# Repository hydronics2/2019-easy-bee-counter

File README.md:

# 2019 Easy Bee Counter V.1

This version of the bee counter is easy to solder and assemble (all through-hole).  It's been tested and works* with sample code provided.

The current tested design is easy to program and approachable to beginner programmers.  The printed circuit board accepts multiple Arduino platforms made by Adafruit including their line of [Adafruit Feather](https://www.adafruit.com/category/777) type micro-controllers and [Adafruit ItsyBitsy](https://www.adafruit.com/category/1008) micro-controllers.   The Adafruit feathers include wifi and long range radio features (*~~esp8266~~, esp32, and **LoRA). All the ItsyBitsy 3V models (M0, M4, and 32u4) should work fine.

*the esp8266 is missing A5 so you have to jumper to another pin
**see below issue with SPI

### [Data Analysis - *why count bees?](https://github.com/hydronics2/2019-easy-bee-counter/blob/master/Data/README.md)
### [Instructions](https://github.com/hydronics2/2019-easy-bee-counter/blob/master/instructions/README.md)
### [Arduino Code](https://github.com/hydronics2/2019-easy-bee-counter/blob/master/arduino/README.md)
### Major Differences/Improvements
- All through-hole components for easy soldering
- Dual footprint, socketed, off-the-shelf micro-controllers => Feather and ItsyBitsy
- Program in Arduino, Lua, and microPython
- A total of 24 gates, 48 sensors, 6 shift registers
- ~14.75" long stretching the entire opening of a langstroth hive for easy placement
- using 2 PCBs to create a sandwich is an inexpensive quick solution. The PCBs must be ordered [black](https://github.com/hydronics2/2019-easy-bee-counter/tree/master/instructions/ordering_instructions) so the IR LED emitter is absorbed into the material.
- using 6 pin headers to create the turn-styles or gates
- N-Ch mosfet controlled IR LEDs such that LEDs can be controlled ON for short periods during while sensing (~75us). Allows for reduced power to less than 1ma (plus micro-controller).

### General Operation
Honeybees are forced through 24 gates where optical sensors (48 sensors) determine whether the bee is present and determine the direction of the bee movement. Each optical sensors has an IR LED and an IR sensor. If no bee is present the IR light is absorbed into the black surface. If a bee is present the IR light reflects off the bee and triggers the sensor. 

### Micro-Controller Pinout
#### Feather ESP32 Pinout

#### ItsyBitsy Pinout

### Shift-in registers
There are 6 shift-in registers. Here's a great description for how to connect and program [shift registers](http://www.gammon.com.au/forum/?id=11979).  The micro-controller's SPI pins read the shift registers. All six shift registers are read at the same time. The sensors are normally pulled low and show 3.3V or HIGH when a transistor is triggered and a bee is present.

Unfortunately the shift registers we're using (the most popular shift register chip!) are not [full SPI devices](https://electronics.stackexchange.com/questions/121249/how-to-put-a-74hc165-on-an-spi-bus) and wont share the SPI with other devices.. They're like the worst SPI devices!... therefore some boards like the Adalogger or LoRa just wont work out of the box. You can still do it by cutting some traces and patching the SPI lines to free pins and bitbanging the SPI to the shift registers.. buy yeah not optimum. You can get a true-spi shift register but the pinout will be different than the 74hc165 used here.

### IR LEDs
The 48 LEDs are divided into two sets of 24 with each set controlled by an N-ch mosfet. The normal forward voltage of each IR LED is 1.2V and about 20ma as shown on the [data sheet](https://www.sparkfun.com/datasheets/Robotics/QR_QRE1113.GR.pdf). Two LEDs are connected in series with a 22ohm resistor. There are jumpers on the board that allow the LEDs to bypass the current limiting resistors. Do not solder the jumper until fully tested! Refer to [these instructions](https://github.com/hydronics2/2019-easy-bee-counter/tree/master/instructions)

### Power
The PCB design connects the USB power pin from the uController to the 3.3V regulator so that a usb cable connected to the micro-controller can power the entire project.

### Bill of Materials
#### uController
The code was tested with the feather esp32 Huzzah and itsyBitsy M0 but will work with all these boards.
- feather Huzzah from [mouser](https://www.mouser.com/ProductDetail/485-3591)
- feather esp8266 from [mouser](https://www.mouser.com/ProductDetail/485-2821)
  - the esp8266 is missing A5, so if this micro is used you have to jumper to another pin
- feather LoRa 900mhz from [mouser](https://www.mouser.com/ProductDetail/485-3178)
- ItsyBitsy M0 from [mouser](https://www.mouser.com/ProductDetail/485-3727)
- ItsyBitsy M4 from [mouser](https://www.mouser.com/ProductDetail/485-3800)
#### PCB
[JLCPCB](https://jlcpcb.com/quote#/) ~$16-25 with shipping. Order the PCBs Black. See [these instructions](https://github.com/hydronics2/2019-easy-bee-counter/tree/master/instructions/ordering_instructions) for ordering.
#### Parts and Pieces from [mouser](https://www.mouser.com/ProjectManager/ProjectDetail.aspx?AccessID=054286973a)
See alternative pricing below for cheaper options specifically for the reflectance sensors.
- [qre1113 Reflective Sensors](https://www.mouser.com/ProductDetail/512-QRE1113f) qty(48)
- [6 pin female headers](https://www.mouser.com/ProductDetail/437-8018700610001101) 7mm high, 0.1" spacing, qty(~36)
- [22ohm resistors](https://www.mouser.com/ProductDetail/Xicon/266-22-RC?qs=sGAEpiMZZMvrmc6UYKmaNXFefT4dxyTCwtpTxTI0yoo%3D), bussed, qty(4)
SIP Packaged, bussed
- [100k ohm resistors](https://www.mouser.com/ProductDetail/IRC-TT-Electronics/L091S104LF?qs=sGAEpiMZZMvrmc6UYKmaNdnTrsZX%2FuSiyGduauH5Qpc%3D) bussed, qty(6)
SIP-9, 8 resistors, 9 pins
- Shift registers, qty(6)
[74HC165](https://www.mouser.com/ProductDetail/595-SN74HC165N)
- [3.3V Regulator](https://www.mouser.com/ProductDetail/Microchip-Technology/MCP1826S-3302E-AB?qs=sGAEpiMZZMsGz1a6aV8DcJ7KfjtCj7Xd5CqQpyOghgk%3D), (input, ground, output - IGO, pinout), qty(1)
- [screw terminals](https://www.mouser.com/ProductDetail/490-TB006-508-02BE) Two pin, 0.1", qty(3)
- [0.1 uF Ceramic Capacitor](https://www.mouser.com/ProductDetail/594-K104K15X7RF53H5), through hole, qty(6)
- [1 uF Ceramic Capacitor](https://www.mouser.com/ProductDetail/594-K105Z20Y5VF5TL2), through hole, qty(1)
- [560uF, 6.3V Capacitor](https://www.mouser.com/ProductDetail/661-APSC6R3L561MH08S)
low esr, 3.5mm lead spacing, 8mm diameter
- N-Channel Mosfet [FQP30N06](https://www.mouser.com/ProductDetail/512-FQP30N06L), qty(2)
  - [chinswain](https://github.com/hydronics2/2019-easy-bee-counter/issues/20#issuecomment-2094117078) suggested using this IRLB8721PbF N-Channel mosfet. He suggested the signal threshold of 3.3V was not sufficient to meet the gate threshold for the FQP30N06L... and it could be the ebay versions of the FQP30N06L floating around are not to spec.

#### Alternative pricing from Chinese distributor LCSC
Someone pointed out some alternative pricing that can really bring the cost down.
- [ITR8307 Reflectance Sensors](https://lcsc.com/product-detail/Photo-Interrupter_Everlight-Elec-ITR8307_C63451.html) ~$0.13/each @ qty(48) (same as QRE1113)
- [6 pin female headers](https://lcsc.com/product-detail/Pin-Header-Female-Header_BOOMELE-Boom-Precision-Elec-C40877_C40877.html) 8.5mm high. ~$0.05/each @ qty(36+)
- [22 ohm SIP](https://lcsc.com/product-detail/Resistor-Networks-Arrays_FH-Guangdong-Fenghua-Advanced-Tech-A09-220JP_C9105.html) 8 resistor, 9 pin, it will fit. $0.44 for qty(4)
- [100k SIP Resistors](https://lcsc.com/product-detail/Resistor-Networks-Arrays_FH-Guangdong-Fenghua-Advanced-Tech-A09-104JP_C9108.html) 8 resistor, 9pin, it will fit. $0.44 for qty(6)

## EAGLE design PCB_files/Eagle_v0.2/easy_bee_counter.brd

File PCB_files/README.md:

## Printed Circuit Board (PCB)

This PCB version has two footprints that accept the wider (0.8") Adafruit Feather micro-controllers such as the [esp32](https://www.adafruit.com/product/3405) and the narrower (0.6")[Adafruit ItsyBitsy](https://www.adafruit.com/category/1008) micro-controllers.

**UPDATE** The GERBER files were developed from the kicad board files so had to remove the gerber files. You now have to use the Eagle board files or generate gerber files from the eagle board files.... or a lot of PCB manufacturers will take eagle PCB files and you don't have to generate your own gerber files. You can still use the kicad files but you have to route a small trace for the SCK pin. See this bug report: https://github.com/hydronics2/2019-easy-bee-counter/issues/25 

These files were created in Autocad EAGLE PCB software. The zipped files are the gerber files needed by the PCB manufacturer.

Right click and 'save link as' to download the files and then upload them to the PCB manufacturer. See the [ordering instructions here](https://github.com/hydronics2/2019-easy-bee-counter/tree/master/instructions/ordering_instructions). Most board shops require a minimum order of 3-5 boards and you'll need 2 boards to sandwich together to complete one bee counter.

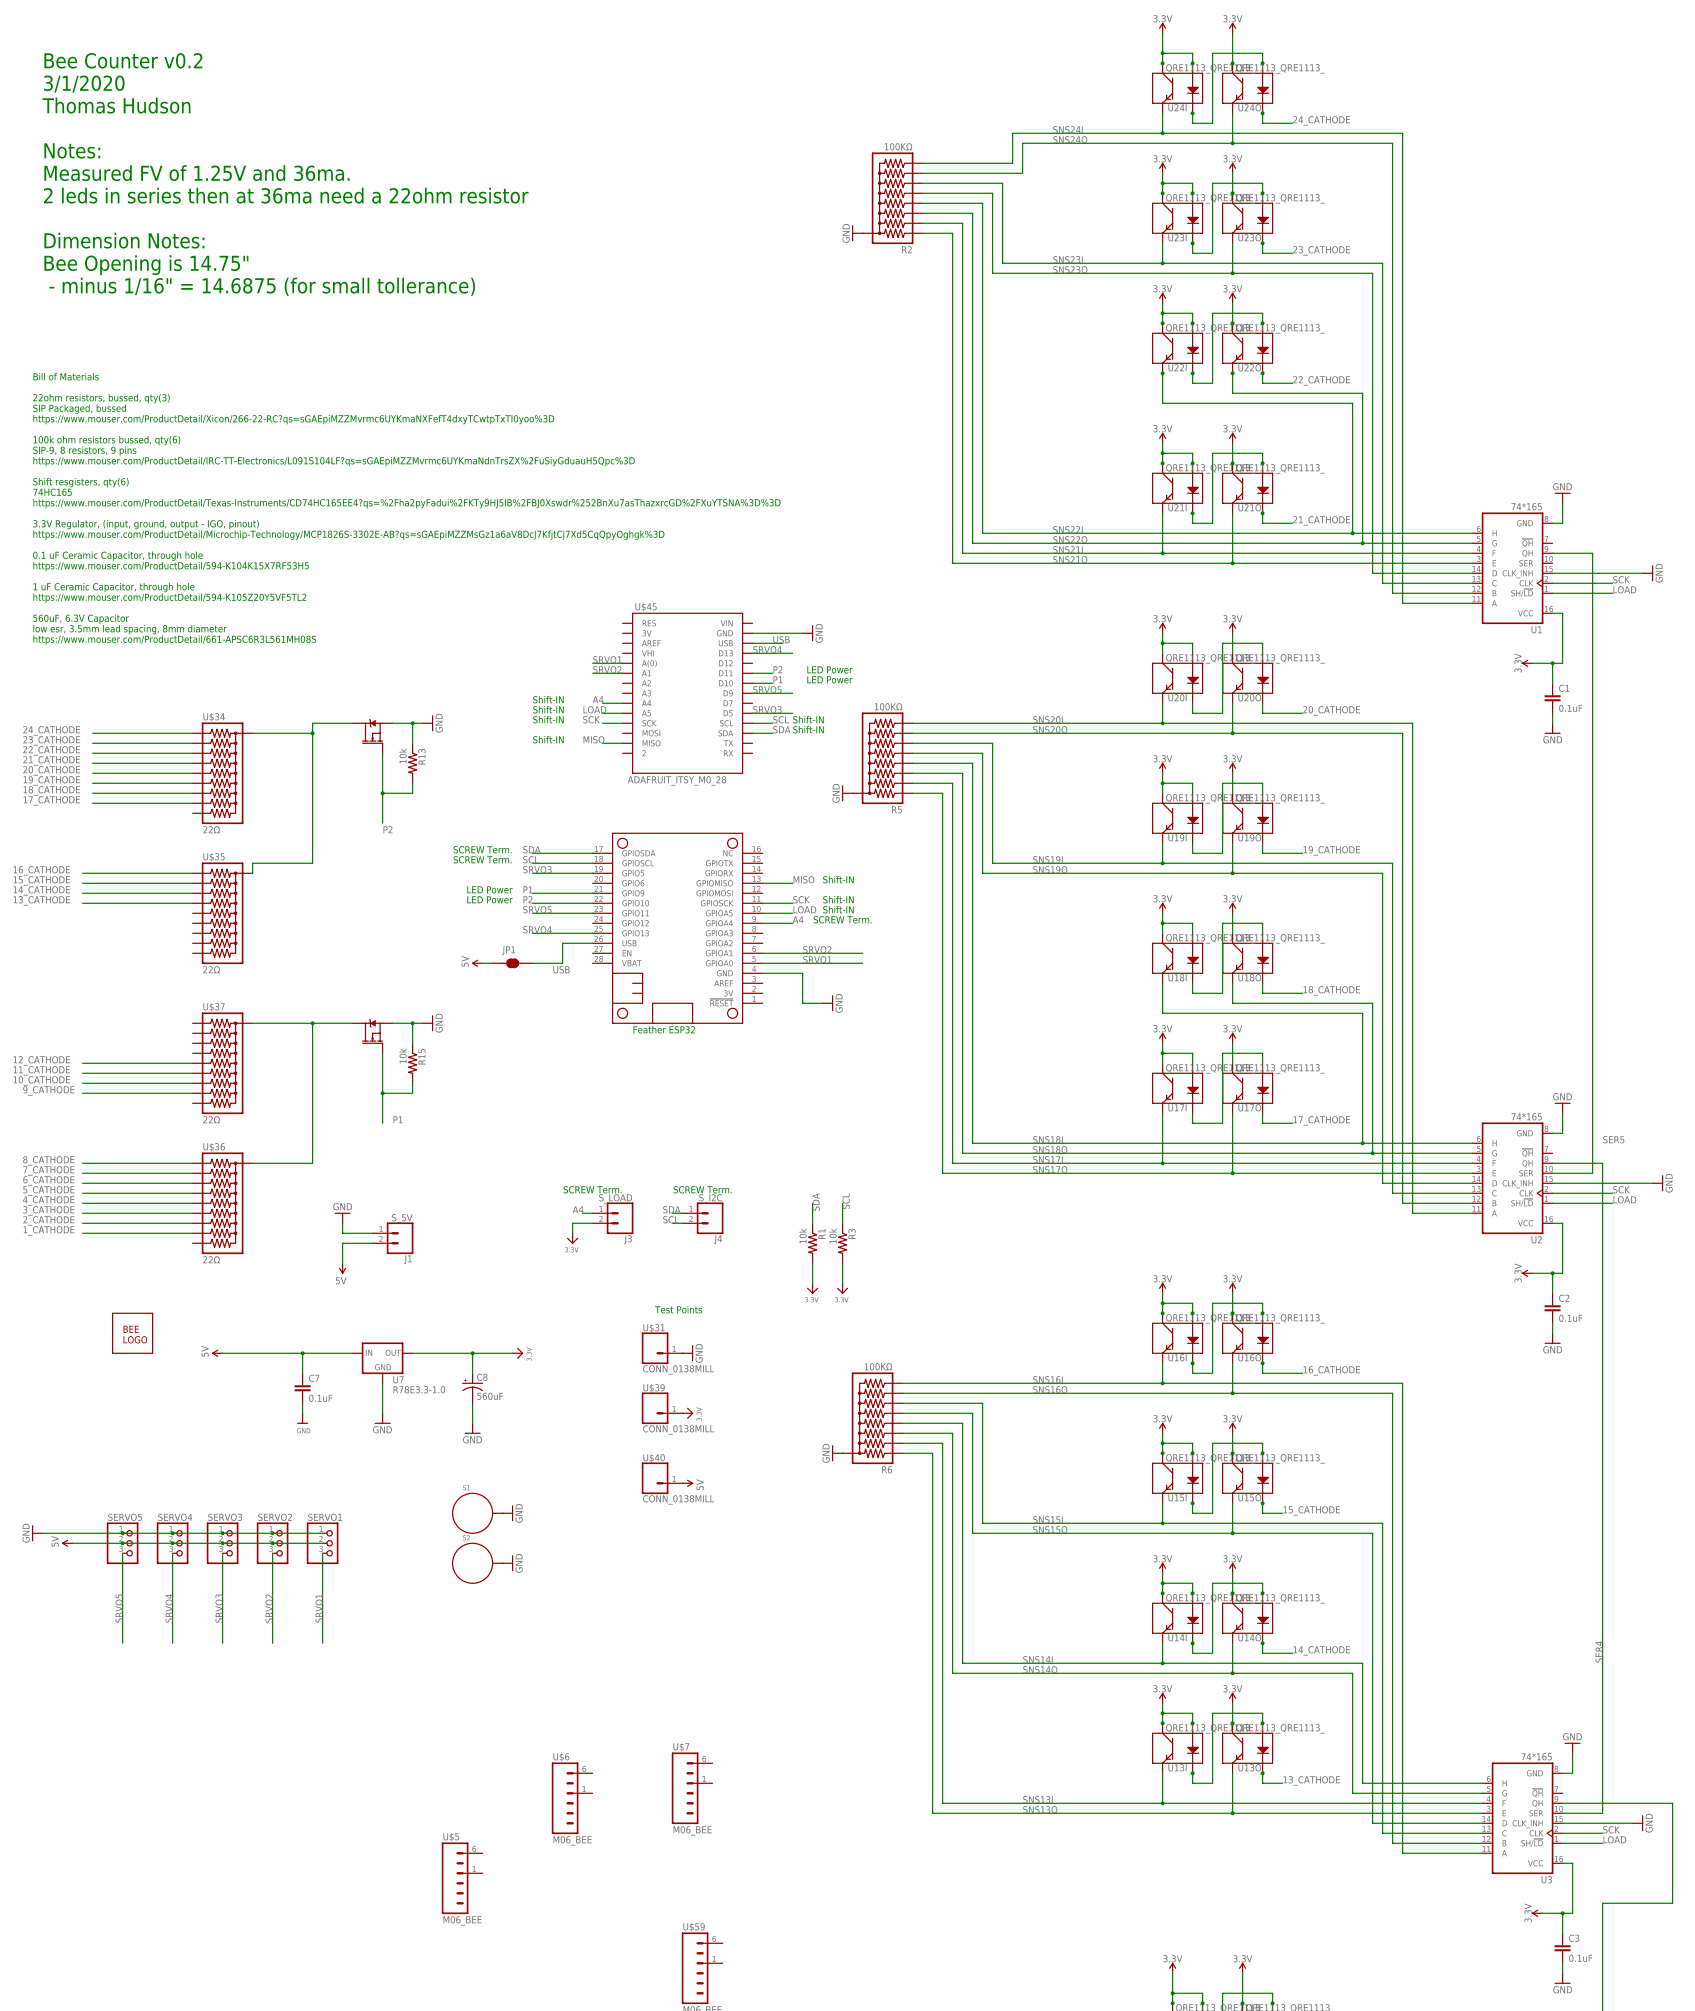
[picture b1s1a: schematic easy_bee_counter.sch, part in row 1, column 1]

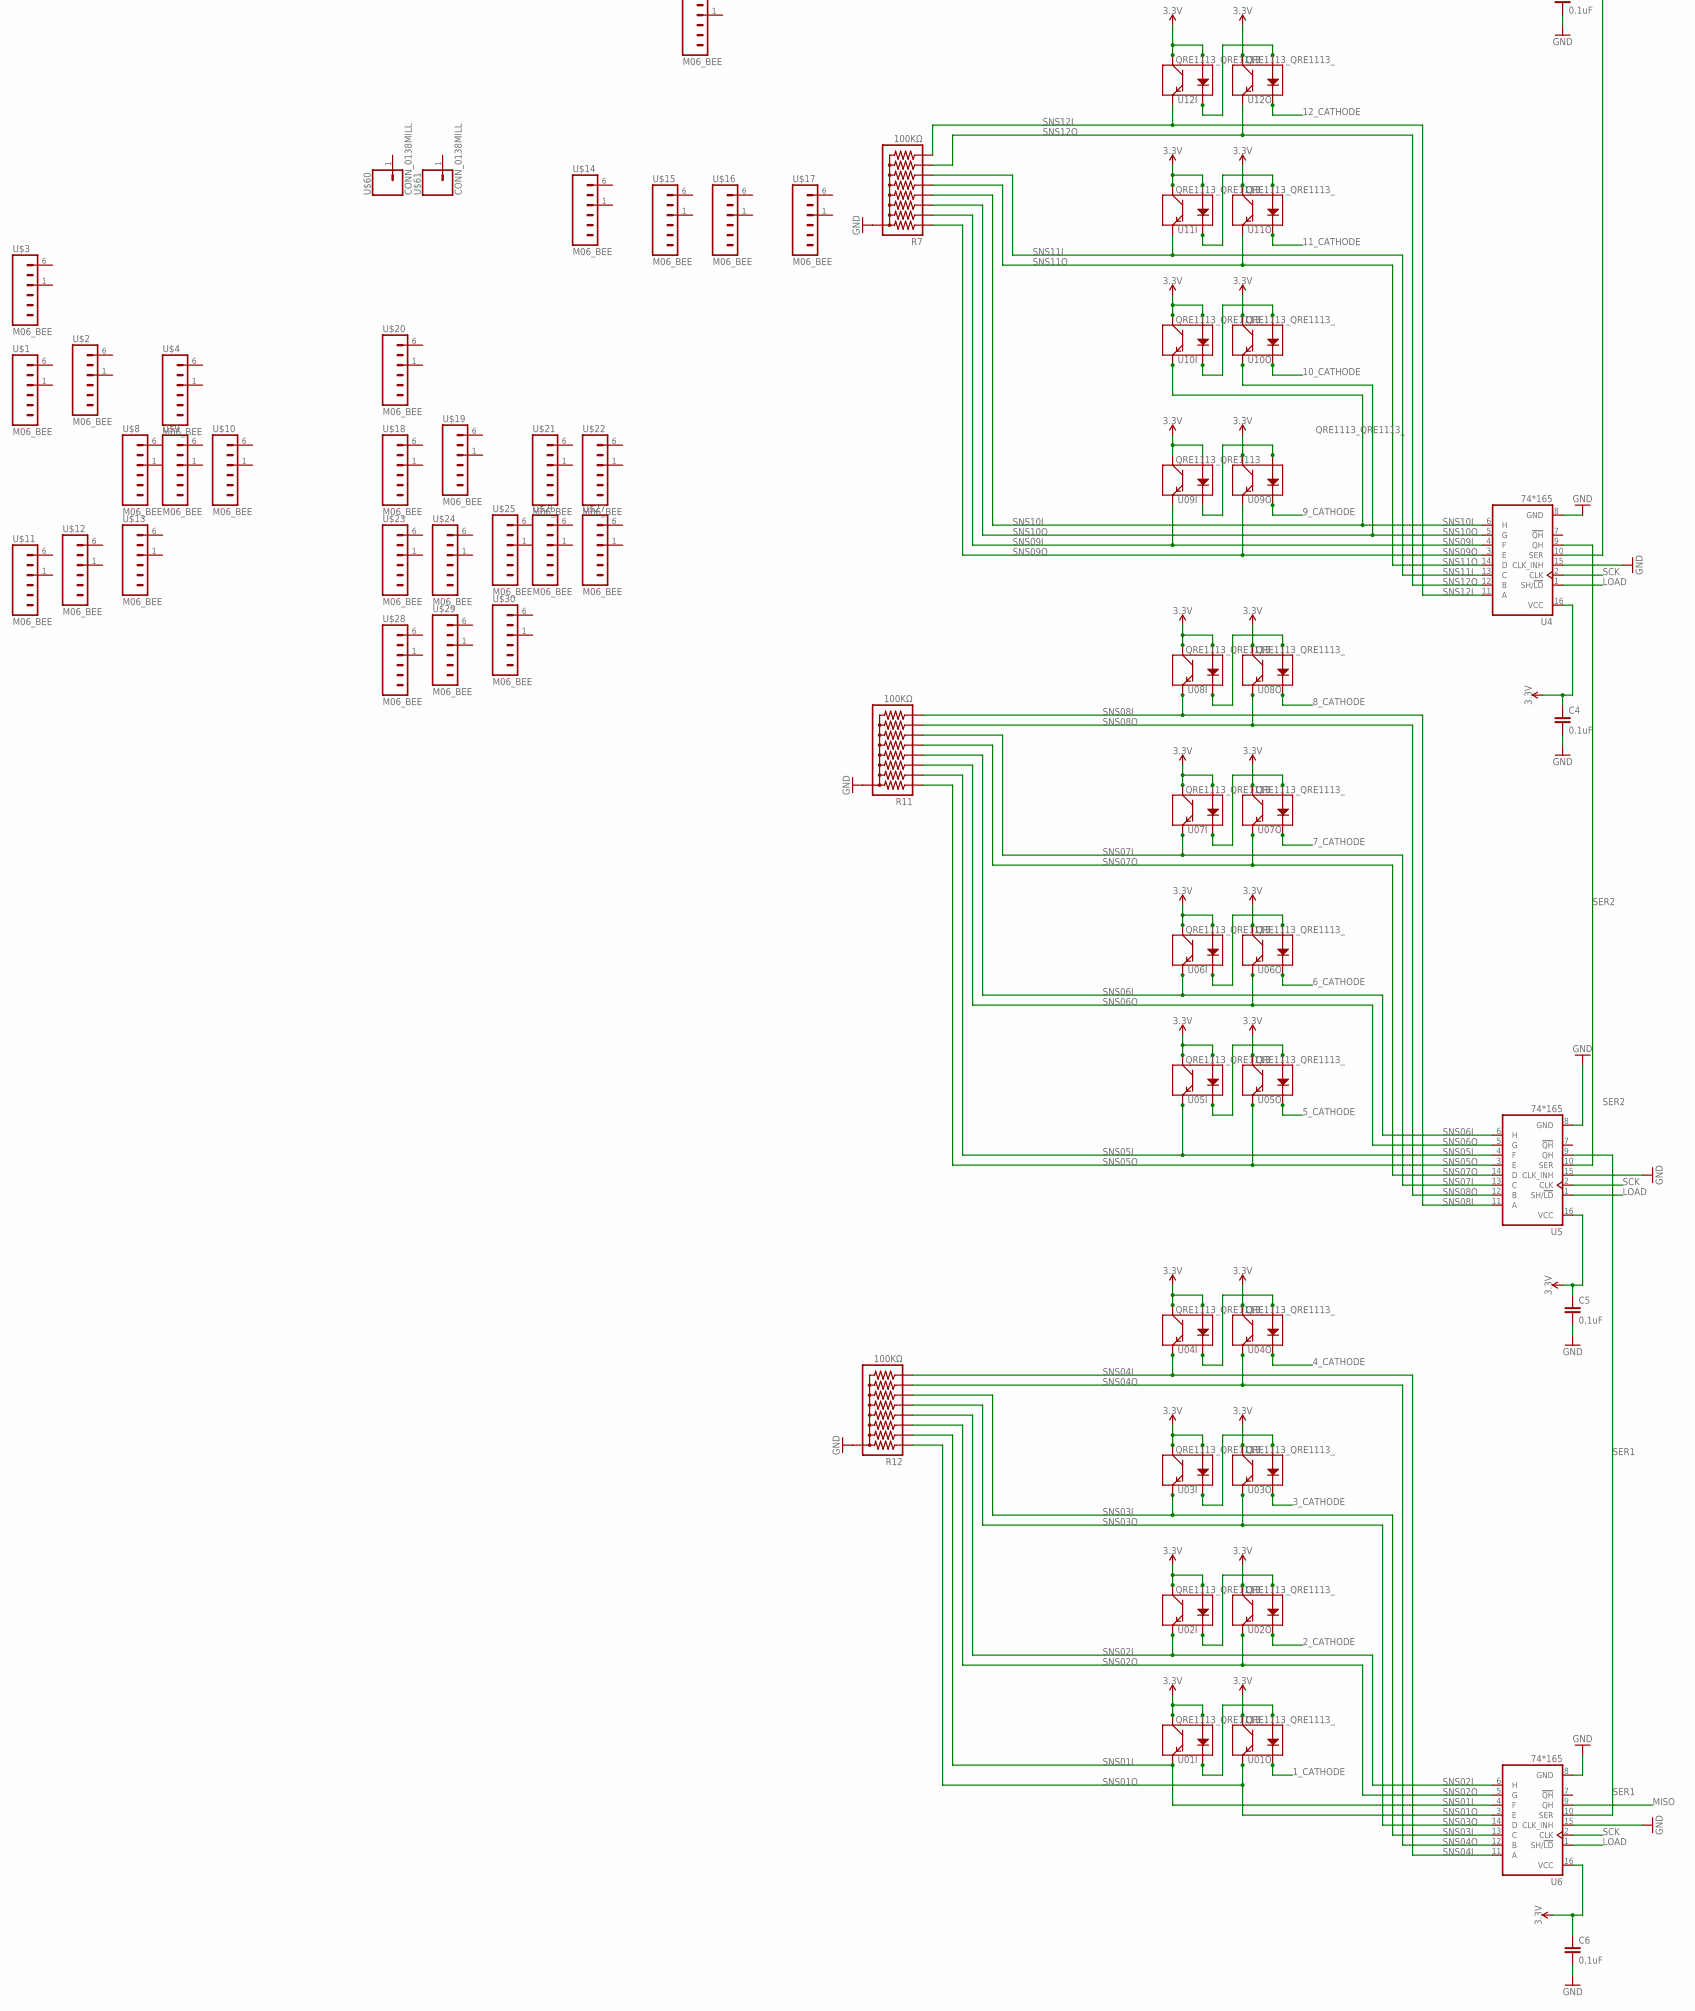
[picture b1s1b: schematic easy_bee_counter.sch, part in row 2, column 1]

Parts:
C1, C2, C3, C4, C5, C6, C7: 0.1uF; CAP-PTH-SMALL-KIT
C8: 560uF; E3,5-8
J1: S_5V; SCREWTERMINAL-5MM-2
J3: S_LOAD; SCREWTERMINAL-5MM-2
J4: S_I2C; SCREWTERMINAL-5MM-2
JP1: JUMPER-SMT_2_NC_TRACE_SILK; SMT-JUMPER_2_NC_TRACE_SILK
MS2: FEATHERWING_NODIM; FEATHERWING_DIM
Q6, Q7: 60V/32A/35mΩ; TO220V
R1, R3, R13, R15: 10k; AXIAL-0.3
R2, R5, R6, R7, R11, R12: 100KΩ; RPACK-SIP-PTH-8
S1, S2: STANDOFF_ELECTRICAL5-32; STANDOFF_ELECTRICAL_5_32
SERVO1, SERVO2, SERVO3, SERVO4, SERVO5: PINHD-1X3; 1X03
U1, U2, U3, U4, U5, U6: 74*165; DIP16
U01I, U01O, U02I, U02O, U03I, U03O, U04I, U04O, U05I, U05O, U06I, U06O, U07I, U07O, U08I, U08O, U09I, U09O, U10I, U10O, U11I, U11O, U12I, U12O, U13I, U13O, U14I, U14O, U15I, U15O, U16I, U16O, U17I, U17O, U18I, U18O, U19I, U19O, U20I, U20O, U21I, U21O, U22I, U22O, U23I, U23O, U24I, U24O: QRE1113_QRE1113_; QRE1113_DIP400W50P180L360H200Q4
U7: R78E3.3-1.0; DC-DC_CONVERTER_78XX
U$1, U$2, U$3, U$4, U$5, U$6, U$7, U$8, U$9, U$10, U$11, U$12, U$13, U$14, U$15, U$16, U$17, U$18, U$19, U$20, U$21, U$22, U$23, U$24, U$25, U$26, U$27, U$28, U$29, U$30, U$59: M06_BEE; 1X06_BEE
U$31, U$39, U$40, U$60, U$61: CONN_0138MILL; 1X01-40MILL
U$34, U$35, U$36, U$37: 22Ω; RPACK-SIP-PTH-9
U$44: BEE_LOGO
U$45: ADAFRUIT_ITSY_M0_28; ADAFRUIT_ITS_MO_28

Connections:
1_CATHODE: U01O.2 (K), U$36.P$9 (9)
2_CATHODE: U02O.2 (K), U$36.P$8 (8)
3.3V: C1.1, C2.1, C3.1, C4.1, C5.1, C6.1, C8.+, J3.2, R1.P$2 (2), R3.P$2 (2), U1.16 (VCC), U01I.1 (A), U01I.3 (C), U01O.3 (C), U2.16 (VCC), U02I.1 (A), U02I.3 (C), U02O.3 (C), U3.16 (VCC), U03I.1 (A), U03I.3 (C), U03O.3 (C), U4.16 (VCC), U04I.1 (A), U04I.3 (C), U04O.3 (C), U5.16 (VCC), U05I.1 (A), U05I.3 (C), U05O.3 (C), U6.16 (VCC), U06I.1 (A), U06I.3 (C), U06O.3 (C), U7.VOUT (OUT), U07I.1 (A), U07I.3 (C), U07O.3 (C), U08I.1 (A), U08I.3 (C), U08O.3 (C), U09I.1 (A), U09I.3 (C), U09O.3 (C), U10I.1 (A), U10I.3 (C), U10O.3 (C), U11I.1 (A), U11I.3 (C), U11O.3 (C), U12I.1 (A), U12I.3 (C), U12O.3 (C), U13I.1 (A), U13I.3 (C), U13O.3 (C), U14I.1 (A), U14I.3 (C), U14O.3 (C), U15I.1 (A), U15I.3 (C), U15O.3 (C), U16I.1 (A), U16I.3 (C), U16O.3 (C), U17I.1 (A), U17I.3 (C), U17O.3 (C), U18I.1 (A), U18I.3 (C), U18O.3 (C), U19I.1 (A), U19I.3 (C), U19O.3 (C), U20I.1 (A), U20I.3 (C), U20O.3 (C), U21I.1 (A), U21I.3 (C), U21O.3 (C), U22I.1 (A), U22I.3 (C), U22O.3 (C), U23I.1 (A), U23I.3 (C), U23O.3 (C), U24I.1 (A), U24I.3 (C), U24O.3 (C), U$39.1
3_CATHODE: U03O.2 (K), U$36.P$7 (7)
4_CATHODE: U04O.2 (K), U$36.P$6 (6)
5V: C7.1, J1.2, JP1.1, SERVO1.2, SERVO2.2, SERVO3.2, SERVO4.2, SERVO5.2, U7.VIN (IN), U$40.1
5_CATHODE: U05O.2 (K), U$36.P$5 (5)
6_CATHODE: U06O.2 (K), U$36.P$4 (4)
7_CATHODE: U07O.2 (K), U$36.P$3 (3)
8_CATHODE: U08O.2 (K), U$36.P$2 (2)
9_CATHODE: U09O.2 (K), U$37.P$9 (9)
10_CATHODE: U10O.2 (K), U$37.P$8 (8)
11_CATHODE: U11O.2 (K), U$37.P$7 (7)
12_CATHODE: U12O.2 (K), U$37.P$6 (6)
13_CATHODE: U13O.2 (K), U$35.P$5 (5)
14_CATHODE: U14O.2 (K), U$35.P$4 (4)
15_CATHODE: U15O.2 (K), U$35.P$3 (3)
16_CATHODE: U16O.2 (K), U$35.P$2 (2)
17_CATHODE: U17O.2 (K), U$34.P$9 (9)
18_CATHODE: U18O.2 (K), U$34.P$8 (8)
19_CATHODE: U19O.2 (K), U$34.P$7 (7)
20_CATHODE: U20O.2 (K), U$34.P$6 (6)
21_CATHODE: U21O.2 (K), U$34.P$5 (5)
22_CATHODE: U22O.2 (K), U$34.P$4 (4)
23_CATHODE: U23O.2 (K), U$34.P$3 (3)
24_CATHODE: U24O.2 (K), U$34.P$2 (2)
A4: J3.1, MS2.9 (GPIOA4), U$45.A4
GND: C1.2, C2.2, C3.2, C4.2, C5.2, C6.2, C7.2, C8.-, J1.1, MS2.4 (GND), Q6.3 (S), Q7.3 (S), R2.P$1 (1), R5.P$1 (1), R6.P$1 (1), R7.P$1 (1), R11.P$1 (1), R12.P$1 (1), R13.P$1 (1), R15.P$1 (1), S1.P1, S2.P1, SERVO1.1, SERVO2.1, SERVO3.1, SERVO4.1, SERVO5.1, U1.8 (GND), U1.15 (CLK_INH), U2.8 (GND), U2.15 (CLK_INH), U3.8 (GND), U3.15 (CLK_INH), U4.8 (GND), U4.15 (CLK_INH), U5.8 (GND), U5.15 (CLK_INH), U6.8 (GND), U6.15 (CLK_INH), U7.GND, U$31.1, U$45.GND
LOAD: MS2.10 (GPIOA5), U1.1 (SH/!LD), U2.1 (SH/!LD), U3.1 (SH/!LD), U4.1 (SH/!LD), U5.1 (SH/!LD), U6.1 (SH/!LD), U$45.A5
MISO: MS2.13 (GPIOMISO), U6.9 (QH), U$45.MISO
unnamed: U11I.2 (K), U11O.1 (A)
unnamed: U12I.2 (K), U12O.1 (A)
unnamed: U10I.2 (K), U10O.1 (A)
unnamed: U09I.2 (K), U09O.1 (A)
unnamed: U05I.2 (K), U05O.1 (A)
unnamed: U06I.2 (K), U06O.1 (A)
unnamed: U08I.2 (K), U08O.1 (A)
unnamed: U04I.2 (K), U04O.1 (A)
unnamed: U07I.2 (K), U07O.1 (A)
unnamed: U03I.2 (K), U03O.1 (A)
unnamed: U02I.2 (K), U02O.1 (A)
unnamed: U01I.2 (K), U01O.1 (A)
unnamed: U24I.2 (K), U24O.1 (A)
unnamed: U23I.2 (K), U23O.1 (A)
unnamed: U22I.2 (K), U22O.1 (A)
unnamed: U21I.2 (K), U21O.1 (A)
unnamed: U17I.2 (K), U17O.1 (A)
unnamed: U18I.2 (K), U18O.1 (A)
unnamed: U20I.2 (K), U20O.1 (A)
unnamed: U19I.2 (K), U19O.1 (A)
unnamed: U16I.2 (K), U16O.1 (A)
unnamed: U15I.2 (K), U15O.1 (A)
unnamed: U14I.2 (K), U14O.1 (A)
unnamed: U13I.2 (K), U13O.1 (A)
P1: MS2.21 (GPIO9), Q7.1 (G), R15.P$2 (2), U$45.D10
P2: MS2.22 (GPIO10), Q6.1 (G), R13.P$2 (2), U$45.D11
PWR_1-12: Q7.2 (D), U$36.P$1 (1), U$37.P$1 (1)
PWR_13-24: Q6.2 (D), U$34.P$1 (1), U$35.P$1 (1)
SCK: MS2.11 (GPIOSCK), U1.2 (CLK), U2.2 (CLK), U3.2 (CLK), U4.2 (CLK), U5.2 (CLK), U6.2 (CLK), U$45.SCK
SCL: J4.2, MS2.18 (GPIOSCL), R3.P$1 (1), U$45.SCL
SDA: J4.1, MS2.17 (GPIOSDA), R1.P$1 (1), U$45.SDA
SER1: U5.9 (QH), U6.10 (SER)
SER2: U4.9 (QH), U5.10 (SER)
SER3: U3.9 (QH), U4.10 (SER)
SER4: U2.9 (QH), U3.10 (SER)
SER5: U1.9 (QH), U2.10 (SER)
SNS01I: R12.P$3 (3), U01I.4 (E), U6.4 (F)
SNS01O: R12.P$2 (2), U01O.4 (E), U6.3 (E)
SNS02I: R12.P$5 (5), U02I.4 (E), U6.6 (H)
SNS02O: R12.P$4 (4), U02O.4 (E), U6.5 (G)
SNS03I: R12.P$7 (7), U03I.4 (E), U6.13 (C)
SNS03O: R12.P$6 (6), U03O.4 (E), U6.14 (D)
SNS04I: R12.P$9 (9), U04I.4 (E), U6.11 (A)
SNS04O: R12.P$8 (8), U04O.4 (E), U6.12 (B)
SNS05I: R11.P$3 (3), U5.4 (F), U05I.4 (E)
SNS05O: R11.P$2 (2), U5.3 (E), U05O.4 (E)
SNS06I: R11.P$5 (5), U5.6 (H), U06I.4 (E)
SNS06O: R11.P$4 (4), U5.5 (G), U06O.4 (E)
SNS07I: R11.P$7 (7), U5.13 (C), U07I.4 (E)
SNS07O: R11.P$6 (6), U5.14 (D), U07O.4 (E)
SNS08I: R11.P$9 (9), U5.11 (A), U08I.4 (E)
SNS08O: R11.P$8 (8), U5.12 (B), U08O.4 (E)
SNS09I: R7.P$3 (3), U4.4 (F), U09I.4 (E)
SNS09O: R7.P$2 (2), U4.3 (E), U09O.4 (E)
SNS10I: R7.P$5 (5), U4.6 (H), U10I.4 (E)
SNS10O: R7.P$4 (4), U4.5 (G), U10O.4 (E)
SNS11I: R7.P$7 (7), U4.13 (C), U11I.4 (E)
SNS11O: R7.P$6 (6), U4.14 (D), U11O.4 (E)
SNS12I: R7.P$9 (9), U4.11 (A), U12I.4 (E)
SNS12O: R7.P$8 (8), U4.12 (B), U12O.4 (E)
SNS13I: R6.P$3 (3), U3.4 (F), U13I.4 (E)
SNS13O: R6.P$2 (2), U3.3 (E), U13O.4 (E)
SNS14I: R6.P$5 (5), U3.6 (H), U14I.4 (E)
SNS14O: R6.P$4 (4), U3.5 (G), U14O.4 (E)
SNS15I: R6.P$7 (7), U3.13 (C), U15I.4 (E)
SNS15O: R6.P$6 (6), U3.14 (D), U15O.4 (E)
SNS16I: R6.P$9 (9), U3.11 (A), U16I.4 (E)
SNS16O: R6.P$8 (8), U3.12 (B), U16O.4 (E)
SNS17I: R5.P$3 (3), U2.4 (F), U17I.4 (E)
SNS17O: R5.P$2 (2), U2.3 (E), U17O.4 (E)
SNS18I: R5.P$5 (5), U2.6 (H), U18I.4 (E)
SNS18O: R5.P$4 (4), U2.5 (G), U18O.4 (E)
SNS19I: R5.P$7 (7), U2.13 (C), U19I.4 (E)
SNS19O: R5.P$6 (6), U2.14 (D), U19O.4 (E)
SNS20I: R5.P$9 (9), U2.11 (A), U20I.4 (E)
SNS20O: R5.P$8 (8), U2.12 (B), U20O.4 (E)
SNS21I: R2.P$3 (3), U1.4 (F), U21I.4 (E)
SNS21O: R2.P$2 (2), U1.3 (E), U21O.4 (E)
SNS22I: R2.P$5 (5), U1.6 (H), U22I.4 (E)
SNS22O: R2.P$4 (4), U1.5 (G), U22O.4 (E)
SNS23I: R2.P$7 (7), U1.13 (C), U23I.4 (E)
SNS23O: R2.P$6 (6), U1.14 (D), U23O.4 (E)
SNS24I: R2.P$9 (9), U1.11 (A), U24I.4 (E)
SNS24O: R2.P$8 (8), U1.12 (B), U24O.4 (E)
SRVO1: MS2.5 (GPIOA0), SERVO1.3, U$45.A0 (A(0))
SRVO2: MS2.6 (GPIOA1), SERVO2.3, U$45.A1
SRVO3: MS2.19 (GPIO5), SERVO3.3, U$45.D5
SRVO4: MS2.25 (GPIO13), SERVO4.3, U$45.D13
SRVO5: MS2.23 (GPIO11), SERVO5.3, U$45.D9
USB: JP1.2, MS2.26 (USB), U$45.USB

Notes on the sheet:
Notes: Measured FV of 1.25V and 36ma. 2 leds in series then at 36ma need a 22ohm resistor Dimension Notes: Bee Opening is 14.75" - minus 1/16" = 14.6875 (for small tollerance)
Bill of Materials 22ohm resistors, bussed, qty(3) SIP Packaged, bussed https://www.mouser.com/ProductDetail/Xicon/266-22-RC?qs=sGAEpiMZZMvrmc6UYKmaNXFefT4dxyTCwtpTxTI0yoo%3D 100k ohm resistors bussed, qty(6) SIP-9, 8 resistors, 9 pins https://www.mouser.com/ProductDetail/IRC-TT-Electronics/L091S104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
Shift-IN
LED Power
SCREW Term.
Test Points
Feather ESP32
Bee Counter v0.2 3/1/2020 Thomas Hudson

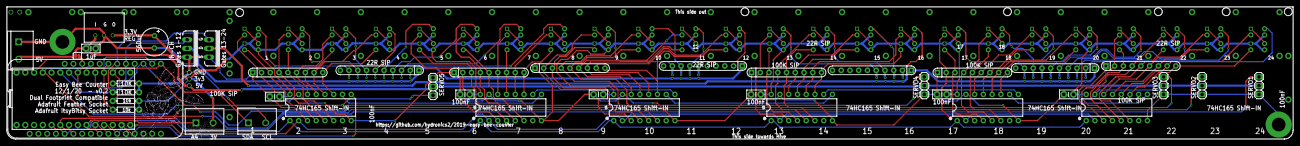
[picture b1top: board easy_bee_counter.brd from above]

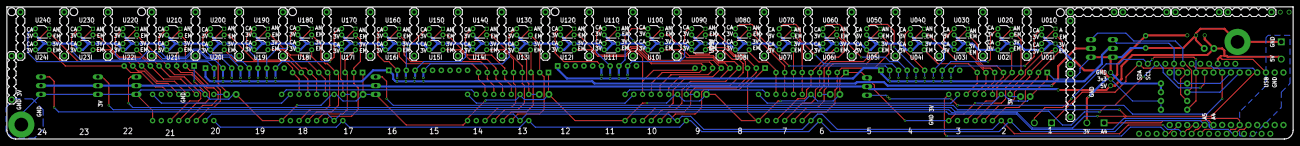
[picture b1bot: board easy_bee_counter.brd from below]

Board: 2 copper layers, 373.4 x 38.4 mm, 129 parts (79 on the bottom side), 120 nets.

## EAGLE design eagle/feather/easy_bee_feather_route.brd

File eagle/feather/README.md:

## FEATEHER Footrprint

This PCB version has a footprint for an Adafruit Feather such as the [esp32](https://www.adafruit.com/product/3405).

These files were created in Autocad EAGLE PCB software. The zipped files are the gerber files needed by the PCB manufacturer.

Right click and 'save link as' to download the files and then upload them to the PCB manufacturer. See the [ordering instructions here](https://github.com/hydronics2/2019-easy-bee-counter/tree/master/instructions/ordering_instructions)

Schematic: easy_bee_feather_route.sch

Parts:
C1, C2, C3, C4, C5, C6: 0.1uF; CAP-PTH-SMALL-KIT
C7: 1uF; CAP-PTH-SMALL-KIT
C8: 560uF; E3,5-8
J1, J3, J4: CONN_025MM; SCREWTERMINAL-5MM-2
JP1: JUMPER-SMT_2_NC_TRACE_SILK; SMT-JUMPER_2_NC_TRACE_SILK
MS2: FEATHERWING_NODIM; FEATHERWING_DIM
Q6, Q7: 60V/32A/35mΩ; TO220V
R2, R5, R6, R7, R11, R12: RPACK-BUSSED-8-SIP-PTH-8; RPACK-SIP-PTH-8
R13, R15: 10k; AXIAL-0.3
S1, S2: STANDOFF_ELECTRICAL5-32; STANDOFF_ELECTRICAL_5_32
U1, U2, U3, U4, U5, U6: 74165; DIP16
U7: V_REG_78XXSINK; TO220-IGO
U$1, U$2, U$3, U$4, U$5, U$6, U$7, U$8, U$9, U$10, U$11, U$12, U$13, U$14, U$15, U$16, U$17, U$18, U$19, U$20, U$21, U$22, U$23, U$24, U$25, U$26, U$27, U$28, U$29, U$30, U$59: M06_BEE; 1X06_BEE
U$31, U$39, U$40, U$60, U$61: CONN_0138MILL; 1X01-40MILL
U$34, U$35, U$36, U$37: RPACK-BUSSED-9; RPACK-SIP-PTH-9
U$68, U$69, U$70, U$71, U$72, U$73, U$74, U$75, U$76, U$77, U$78, U$79, U$80, U$81, U$82, U$83, U$84, U$85, U$86, U$87, U$88, U$89, U$90, U$91, U$92, U$93, U$94, U$95, U$96, U$97, U$98, U$99, U$100, U$101, U$102, U$103, U$104, U$105, U$106, U$107, U$108, U$109, U$110, U$111, U$112, U$113, U$114, U$115: QRE1113_; DIP400W50P180L360H200Q4

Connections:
1_CATHODE: U$36.P$9 (9), U$115.2 (K)
2_CATHODE: U$36.P$8 (8), U$113.2 (K)
3.3V: C1.1, C2.1, C3.1, C4.1, C5.1, C6.1, C8.+, J3.2, U1.16 (VCC), U2.16 (VCC), U3.16 (VCC), U4.16 (VCC), U5.16 (VCC), U6.16 (VCC), U7.OUT, U$39.1, U$68.1 (A), U$68.3 (C), U$69.3 (C), U$70.1 (A), U$70.3 (C), U$71.3 (C), U$72.1 (A), U$72.3 (C), U$73.3 (C), U$74.1 (A), U$74.3 (C), U$75.3 (C), U$76.1 (A), U$76.3 (C), U$77.3 (C), U$78.1 (A), U$78.3 (C), U$79.3 (C), U$80.1 (A), U$80.3 (C), U$81.3 (C), U$82.1 (A), U$82.3 (C), U$83.3 (C), U$84.1 (A), U$84.3 (C), U$85.3 (C), U$86.1 (A), U$86.3 (C), U$87.3 (C), U$88.1 (A), U$88.3 (C), U$89.3 (C), U$90.1 (A), U$90.3 (C), U$91.3 (C), U$92.1 (A), U$92.3 (C), U$93.3 (C), U$94.1 (A), U$94.3 (C), U$95.3 (C), U$96.1 (A), U$96.3 (C), U$97.3 (C), U$98.1 (A), U$98.3 (C), U$99.3 (C), U$100.1 (A), U$100.3 (C), U$101.3 (C), U$102.1 (A), U$102.3 (C), U$103.3 (C), U$104.1 (A), U$104.3 (C), U$105.3 (C), U$106.1 (A), U$106.3 (C), U$107.3 (C), U$108.1 (A), U$108.3 (C), U$109.3 (C), U$110.1 (A), U$110.3 (C), U$111.3 (C), U$112.1 (A), U$112.3 (C), U$113.3 (C), U$114.1 (A), U$114.3 (C), U$115.3 (C)
3_CATHODE: U$36.P$7 (7), U$111.2 (K)
4_CATHODE: U$36.P$6 (6), U$109.2 (K)
5V: C7.1, J1.2, JP1.1, MS2.28 (VBAT), U7.IN, U$40.1
5_CATHODE: U$36.P$5 (5), U$107.2 (K)
6_CATHODE: U$36.P$4 (4), U$105.2 (K)
7_CATHODE: U$36.P$3 (3), U$103.2 (K)
8_CATHODE: U$36.P$2 (2), U$101.2 (K)
9_CATHODE: U$37.P$9 (9), U$99.2 (K)
10_CATHODE: U$37.P$8 (8), U$97.2 (K)
11_CATHODE: U$37.P$7 (7), U$95.2 (K)
12_CATHODE: U$37.P$6 (6), U$93.2 (K)
13_CATHODE: U$35.P$5 (5), U$91.2 (K)
14_CATHODE: U$35.P$4 (4), U$89.2 (K)
15_CATHODE: U$35.P$3 (3), U$87.2 (K)
16_CATHODE: U$35.P$2 (2), U$85.2 (K)
17_CATHODE: U$34.P$9 (9), U$83.2 (K)
18_CATHODE: U$34.P$8 (8), U$81.2 (K)
19_CATHODE: U$34.P$7 (7), U$79.2 (K)
20_CATHODE: U$34.P$6 (6), U$77.2 (K)
21_CATHODE: U$34.P$5 (5), U$75.2 (K)
22_CATHODE: U$34.P$4 (4), U$73.2 (K)
23_CATHODE: U$34.P$3 (3), U$71.2 (K)
24_CATHODE: U$34.P$2 (2), U$69.2 (K)
A0: MS2.5 (GPIOA0), U4.15 (CLK_INH), U5.15 (CLK_INH), U6.15 (CLK_INH)
A1: MS2.6 (GPIOA1), U1.15 (CLK_INH), U2.15 (CLK_INH), U3.15 (CLK_INH)
A2: MS2.7 (GPIOA2)
A3: MS2.8 (GPIOA3)
A4: J3.1, MS2.9 (GPIOA4)
D9: MS2.21 (GPIO9), Q7.1 (G), R15.P$2 (2)
D10: MS2.22 (GPIO10), Q6.1 (G), R13.P$2 (2)
GND: C1.2, C2.2, C3.2, C4.2, C5.2, C6.2, C7.2, C8.-, J1.1, MS2.4 (GND), Q6.3 (S), Q7.3 (S), R2.P$1 (1), R5.P$1 (1), R6.P$1 (1), R7.P$1 (1), R11.P$1 (1), R12.P$1 (1), R13.P$1 (1), R15.P$1 (1), S1.P1, S2.P1, U1.8 (GND), U2.8 (GND), U3.8 (GND), U4.8 (GND), U5.8 (GND), U6.8 (GND), U7.GND, U$31.1
LOAD: MS2.10 (GPIOA5), U1.1 (SH/!LD), U2.1 (SH/!LD), U3.1 (SH/!LD), U4.1 (SH/!LD), U5.1 (SH/!LD), U6.1 (SH/!LD)
MISO: MS2.13 (GPIOMISO), U3.9 (QH), U6.9 (QH)
MOSI: MS2.12 (GPIOMOSI)
unnamed: U$94.2 (K), U$95.1 (A)
unnamed: U$92.2 (K), U$93.1 (A)
unnamed: U$96.2 (K), U$97.1 (A)
unnamed: U$98.2 (K), U$99.1 (A)
unnamed: U$106.2 (K), U$107.1 (A)
unnamed: U$104.2 (K), U$105.1 (A)
unnamed: U$100.2 (K), U$101.1 (A)
unnamed: U$108.2 (K), U$109.1 (A)
unnamed: U$102.2 (K), U$103.1 (A)
unnamed: U$110.2 (K), U$111.1 (A)
unnamed: R5.P$9 (9), U2.6 (H), U$77.4 (E)
unnamed: U$112.2 (K), U$113.1 (A)
unnamed: U$114.2 (K), U$115.1 (A)
unnamed: R6.P$3 (3), U3.11 (A), U$90.4 (E)
unnamed: R6.P$2 (2), U3.12 (B), U$91.4 (E)
unnamed: R6.P$4 (4), U3.13 (C), U$88.4 (E)
unnamed: R12.P$6 (6), U6.3 (E), U$110.4 (E)
unnamed: R6.P$5 (5), U3.14 (D), U$89.4 (E)
unnamed: R6.P$8 (8), U3.5 (G), U$84.4 (E)
unnamed: Q6.2 (D), U$34.P$1 (1), U$35.P$1 (1)
unnamed: R6.P$9 (9), U3.6 (H), U$85.4 (E)
unnamed: R6.P$6 (6), U3.3 (E), U$86.4 (E)
unnamed: R6.P$7 (7), U3.4 (F), U$87.4 (E)
unnamed: R5.P$4 (4), U2.13 (C), U$80.4 (E)
unnamed: R5.P$5 (5), U2.14 (D), U$81.4 (E)
unnamed: R5.P$8 (8), U2.5 (G), U$76.4 (E)
unnamed: R5.P$6 (6), U2.3 (E), U$78.4 (E)
unnamed: R12.P$3 (3), U6.11 (A), U$114.4 (E)
unnamed: R5.P$7 (7), U2.4 (F), U$79.4 (E)
unnamed: R5.P$3 (3), U2.12 (B), U$83.4 (E)
unnamed: R7.P$4 (4), U4.13 (C), U$96.4 (E)
unnamed: R5.P$2 (2), U2.11 (A), U$82.4 (E)
unnamed: R2.P$7 (7), U1.13 (C), U$72.4 (E)
unnamed: R2.P$6 (6), U1.14 (D), U$73.4 (E)
unnamed: R2.P$5 (5), U1.5 (G), U$68.4 (E)
unnamed: R2.P$4 (4), U1.6 (H), U$69.4 (E)
unnamed: R2.P$2 (2), U1.3 (E), U$70.4 (E)
unnamed: R2.P$3 (3), U1.4 (F), U$71.4 (E)
unnamed: R2.P$8 (8), U1.12 (B), U$75.4 (E)
unnamed: R2.P$9 (9), U1.11 (A), U$74.4 (E)
unnamed: U$68.2 (K), U$69.1 (A)
unnamed: U$70.2 (K), U$71.1 (A)
unnamed: U$72.2 (K), U$73.1 (A)
unnamed: U$74.2 (K), U$75.1 (A)
unnamed: U$82.2 (K), U$83.1 (A)
unnamed: U$80.2 (K), U$81.1 (A)
unnamed: U$76.2 (K), U$77.1 (A)
unnamed: U$78.2 (K), U$79.1 (A)
unnamed: U$84.2 (K), U$85.1 (A)
unnamed: U$86.2 (K), U$87.1 (A)
unnamed: U$88.2 (K), U$89.1 (A)
unnamed: U$90.2 (K), U$91.1 (A)
unnamed: R12.P$7 (7), U6.4 (F), U$111.4 (E)
unnamed: R7.P$8 (8), U4.5 (G), U$92.4 (E)
unnamed: Q7.2 (D), U$36.P$1 (1), U$37.P$1 (1)
unnamed: R7.P$6 (6), U4.3 (E), U$94.4 (E)
unnamed: R7.P$2 (2), U4.11 (A), U$98.4 (E)
unnamed: R11.P$3 (3), U5.12 (B), U$107.4 (E)
unnamed: R12.P$2 (2), U6.12 (B), U$115.4 (E)
unnamed: R11.P$4 (4), U5.13 (C), U$104.4 (E)
unnamed: R11.P$8 (8), U5.5 (G), U$100.4 (E)
unnamed: R11.P$6 (6), U5.3 (E), U$102.4 (E)
unnamed: R11.P$2 (2), U5.11 (A), U$106.4 (E)
unnamed: R12.P$4 (4), U6.13 (C), U$112.4 (E)
unnamed: R12.P$5 (5), U6.14 (D), U$113.4 (E)
unnamed: R11.P$5 (5), U5.14 (D), U$105.4 (E)
unnamed: R12.P$8 (8), U6.5 (G), U$108.4 (E)
unnamed: R12.P$9 (9), U6.6 (H), U$109.4 (E)
unnamed: R11.P$9 (9), U5.6 (H), U$101.4 (E)
unnamed: R11.P$7 (7), U5.4 (F), U$103.4 (E)
unnamed: R7.P$5 (5), U4.14 (D), U$97.4 (E)
unnamed: R7.P$9 (9), U4.6 (H), U$93.4 (E)
unnamed: R7.P$7 (7), U4.4 (F), U$95.4 (E)
unnamed: R7.P$3 (3), U4.12 (B), U$99.4 (E)
SCK: MS2.11 (GPIOSCK), U1.2 (CLK), U2.2 (CLK), U3.2 (CLK), U4.2 (CLK), U5.2 (CLK), U6.2 (CLK)
SCL: J4.2, MS2.18 (GPIOSCL)
SDA: J4.1, MS2.17 (GPIOSDA)
SER1: U5.9 (QH), U6.10 (SER)
SER2: U4.9 (QH), U5.10 (SER)
SER3: U2.9 (QH), U3.10 (SER)
SER4: U1.9 (QH), U2.10 (SER)
USB: JP1.2, MS2.26 (USB)

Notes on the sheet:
Notes: Measured FV of 1.25V and 36ma. 2 leds in series then at 36ma need a 22ohm resistor Dimension Notes: Bee Opening is 14.75" - minus 1/16" = 14.6875 (for small tollerance)
Bill of Materials 22ohm resistors, bussed, qty(3) SIP Packaged, bussed https://www.mouser.com/ProductDetail/Xicon/266-22-RC?qs=sGAEpiMZZMvrmc6UYKmaNXFefT4dxyTCwtpTxTI0yoo%3D 100k ohm resistors bussed, qty(6) SIP-9, 8 resistors, 9 pins https://www.mouser.com/ProductDetail/IRC-TT-Electronics/L091S104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
Shift-IN Chip Select #1, D26 for Huzzah
Shift-IN Chip Select #2, D25 for Huzzah
Shift-IN
LED Power
SCREW Term.
Test Points

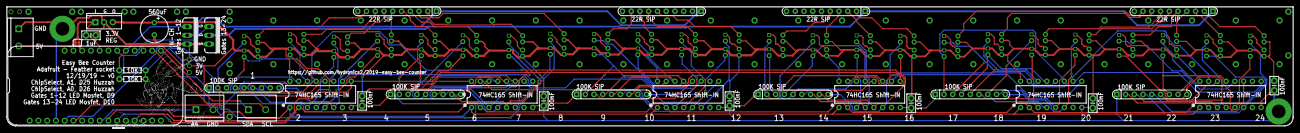
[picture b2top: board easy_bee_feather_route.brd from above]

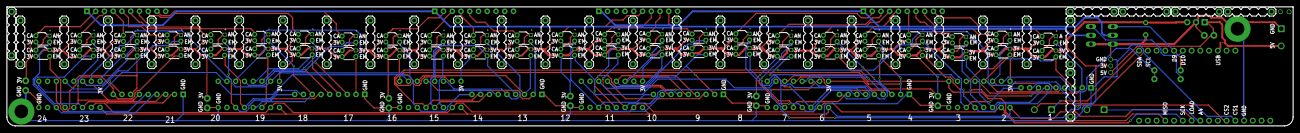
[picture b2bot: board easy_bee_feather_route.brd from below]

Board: 2 copper layers, 373.4 x 34.5 mm, 120 parts (79 on the bottom side), 116 nets.

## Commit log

2019-12-15 Create description
2020-02-22 updated SIP 22ohm resistors to qty(4)
2020-02-22 updated shift register link to quantities small
2020-02-22 update part quantities
2020-03-14 not_sure
2020-03-15 version1
    updated with version 1 Feather only and kicad design files
2020-03-15 add video
2020-03-15 udpates
2020-03-15 updated instructions
2020-03-15 still working on PCB files
2020-03-15 new gerber view
2020-03-15 update pics
2020-03-15 add data
2020-03-15 data
2020-03-16 readme updates
2020-03-16 updated code with itsybitsy power pins
2020-03-16 add gerbers
2020-03-16 update readmes'
2020-03-17 updated blinking IR leds
2020-03-17 new pic
2020-03-17 add instructions video
2020-03-23 Converted Bee Logo into an Eagle Part
    Here's a library containing a single device which has 1 symbol and 1 package.
    The symbol is a simple rectangle that shows up in the schematic and says "Bee Logo".
    Adding the device in the schematic editor will create a copy of the image in the schematic which can be grabbed by the Anchor at the lower left corner and easily moved around for placement on the PCB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
    The Bee Logo itself is in the TPlace layer (as was the original Bee Logo). The anchor for dragging it around is in the Reference layer so that the anchor doesn't get printed on the actual silk screen.
    Mirroring the logo will automatically move it to the BPlace layer as well.
2020-03-23 SN74HC165N
2020-03-23 added info
2020-03-30 Converted Logo to library part Added vias to be solded bridged for jumpers to bypass the SIP resistors. Rerouted the board, realigned many of the parts.
2020-03-30 Added jumpers for 13-24 (oops). Added Tkeepout areas to expose jumpers on component side.
2020-03-30 cleaned up some additional errors.
2020-04-25 removed chipselect pins in bee-counter code
2020-04-25 added kiCad_files
2020-04-25 added gerbers
2020-04-26 updated gerber files
2020-04-26 re-uploaded the gerbers
    the last zip file was corrupt for some reason
2020-04-28 updated gerber download instructions
2020-05-01 removed a duplicate file
2020-05-01 re-output gerber files
    JLCPCB indicated in an email that something was wrong with the gerber files. Seemed to upload fine. OSHPark said they were missing the copper layer which was strange.. Re-output gerber files based on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
2020-05-05 Create featherhuzzah_bee_counter_WiFi
2020-05-05 Update featherhuzzah_bee_counter_WiFi
2020-05-06 Create easy_bee_counter.lbr
    added libraries from ULP export from eagle file
2020-05-08 Reworked connections to 74*165s to put the sense pins in a better order for the board layout.
2020-05-11 Finalized all connections on schematic (missed some sensors last commit). Fully routed board using new component names and new pinouts for SIP packs.
2020-05-11 Corrected unusable pins for servos
2020-05-11 Improvements to test_shift_registers.ino Works with new serial pinout Optimized code quite a bit, removed repetitive code. Added ability to remap serial pinout by editing simple binary array. Set up 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
2020-05-11 Improved clarity in documentation at beginning of file.
2020-05-12 Ported to new pin map Optimized code similarly to previous efforts on test_shift_registers sketch I believe there are other opportunities for optimization, but this took care of the low hanging fruit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
2020-05-12 Added conditional compile for board rev
2020-05-20 note on using the esp8266
    pin A5 is missing!
2020-07-21 added python sample code
2020-08-01 added the detail that the LoRa module
    the LoRa module also requires SPI so you need true SPI chips with the LoRa.
2021-03-01 Update README.md
    updated the readMe detailing issues with the 74HC165 not being a true SPI device
2024-03-07 Update README.MD
    The GERBER files were developed from the kicad board files so had to remove the gerber files. You now have to use the Eagle board files or generate gerber files from the eagle board files.
    https://github.com/hydronics2/2019-easy-bee-counter/issues/25
2024-03-07 Update README.md
    The GERBER files were developed from the kicad board files so had to remove the gerber files. You now have to use the Eagle board files or generate gerber files from the eagle board files.... or a lo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
2024-03-07 Delete PCB_files/gerbers2.zip
    The GERBER files were developed from the kicad board files and there was a small error in the kiCAD files... so the gerber files have been removed. You now have to use the Eagle board files or genera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
2024-03-07 Delete PCB_files/Kicad_v/gerbers directory
    The GERBER files were developed from the kicad board files and there was a small error in the kiCAD files... so the gerber files have been removed. You now have to use the Eagle board files or genera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
2024-03-07 Create read.me
    There is a small error in the kiCAD files... You now have to use the Eagle board files or generate gerber files from the eagle board files.... or a lot of PCB manufacturers will take eagle PCB files 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
2024-03-07 Create README.md
    see message
2024-05-05 Update README.md
    added alternative N-channel mosfet suggestion IRLB8721PbF.
2024-05-05 Update README.md
    update description of the N-channel mosfet

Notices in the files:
parts and their libraries:
SparkFun-Passives: Licensing: Creative Commons ShareAlike 4.0 International - https://creativecommons.org/licenses/by-sa/4.0
microbuilder: This work is placed in the public domain, and may be freely used for commercial and non-commercial work with the following conditions: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
